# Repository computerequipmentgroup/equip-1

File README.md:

# Equip-1 ⚹ DV RECORDER

Equip-1 is an open-source, portable DV/HDV recorder for camcorders with FireWire/i.LINK/DV output. It is built around a Radxa ROCK 2F and a custom PCIe FireWire HAT, so you can mount it near a camera, power it from USB-C, press one button, and record tape footage directly to removable storage.

The project is for camera enthusiasts, videographers, film schools, archivists, and hardware/software contributors who want a modern, repairable path for capturing DV tapes without keeping an old laptop alive.

The [Firehat](https://github.com/computerequipmentgroup/firehat) is also available standalone. It works as a HAT for the ROCK 2F, Raspberry Pi 5, and other SBCs.

Website: <https://www.equip-1.c-e.group/>  
Community: [discord.gg/wpXmcb5mvK](https://discord.gg/wpXmcb5mvK)

## Features

- One-button DV/HDV capture from FireWire camcorders.
- On-device OLED/buttons UI + web based controls.
- Web UI controls for recording, video preview, file management and conversion settings.
- Full-quality `.mov`, `.dv`, `.avi`, or native HDV `.m2t` recordings.
- On-demand or automatic MP4 conversions for easy previewing and sharing.
- Optional MP4 deinterlacing for cleaner playback from interlaced DV sources.
- USB/SD capture storage handling, in-app updates, and HDMI preview support.

## Getting started

### 1. Download and flash a release image

The recommended way to get started is to use a prebuilt Equip-1 image from GitHub Releases.

1. Open the releases page: <https://github.com/computerequipmentgroup/equip-1/releases>
2. Download the latest image for your hardware; Equip-1 uses the Rock 2F image.
3. Install and open [balenaEtcher](https://etcher.balena.io/).
4. In Etcher, choose the Equip-1 image, choose your microSD card, then click **Flash**.
5. When flashing is complete, eject the card, insert it into Equip-1, and power the device over USB-C.

To build and flash an image from source instead:

```bash
./src/buildroot/scripts/build.sh
./src/buildroot/scripts/flash.sh
```

The default runtime settings are baked into the image from:

```text
src/buildroot/overlay/etc/equip1/equip-1.ini
```

On a running device, edit the live settings file at:

```text
/etc/equip1/equip-1.ini
```

### 2. Connect to Equip-1

Default device access:

| Setting        | Default                |
| -------------- | ---------------------- |
| Wi-Fi SSID     | `Equip-1`              |
| Wi-Fi password | `firesecret`           |
| Dashboard      | `http://10.42.0.1/`    |
| API base       | `http://10.42.0.1/api` |

Connect a phone or laptop to the Equip-1 Wi-Fi network, open the dashboard, attach a FireWire DV/HDV camera, and use the web UI or the device buttons to preview and record.

### 3. Prepare capture storage

Equip-1 records to `/data/captures` by default. At boot it prefers a non-root exFAT USB-A drive labelled `EQUIP1`; otherwise it falls back to the SD-card data partition. On a freshly flashed compressed image, first boot creates the missing SD-card recordings partition in the remaining free space, formats it as exFAT, labels it `EQUIP1`, and mounts it at `/data`.

Recommended capture storage format:

- filesystem: exFAT
- label: `EQUIP1`
- mount point on device: `/data`
- captures path: `/data/captures`

If automatic provisioning fails and the UI shows only rootfs-sized free space, create one exFAT partition labelled `EQUIP1` in the unallocated space after the flashed image partitions. Do not modify the boot/rootfs partitions and do not create two exFAT data partitions.

### 4. Record and export

Completed DV recordings are written as full-quality `.mov` captures by default, with settings for raw `.dv` or `.avi` containers. HDV sources still record as native `.m2t`. MP4 sidecars can be created on demand from settings, or automatically after each recording if auto-MP4 export is enabled.

MP4 quality presets:

| Setting    | OLED label | Use                                  |
| ---------- | ---------- | ------------------------------------ |
| `small`    | `[28]`     | Smallest files                       |
| `balanced` | `[23]`     | Middle ground                        |
| `high`     | `[18]`     | Close to source for most DV material |
| `max`      | `[14]`     | Highest quality, larger and slower   |

See [`src/docs/mp4-export.md`](src/docs/mp4-export.md) for the full export flow.

## Runtime settings

User-facing device settings live at `/etc/equip1/equip-1.ini`. The default file is staged from `src/buildroot/overlay/etc/equip1/equip-1.ini`, and matching `EQUIP1_*` environment variables can override INI values for development or one-off debugging.

Example:

```ini
[network]
ap_ssid = Equip-1
ap_password = firesecret

[recording]
capture_dir = /data/captures
storage_label = EQUIP1
recording_format = mov
auto_convert_mp4 = false
mp4_quality = high
mp4_deinterlace = true
auto_storage_switch = true

[hdmi]
enabled = true

[logging]
log_level = info
```

## Docs

The full source documentation lives in `src/docs/` and covers the runtime settings, capture pipeline, storage behavior, user interfaces, and Buildroot image. Start with the topic that matches what you are changing, then follow the linked references for lower-level implementation details.

- [`src/docs/runtime-settings.md`](src/docs/runtime-settings.md) — `/etc/equip1/equip-1.ini` sections, common keys, and environment overrides.
- [`src/docs/mp4-export.md`](src/docs/mp4-export.md) — MP4 sidecar export flow, OLED labels, and quality presets.
- [`src/docs/storage-captures-usb.md`](src/docs/storage-captures-usb.md) — capture storage, `/data/captures`, USB switching, and USB-C mass-storage mode.
- [`src/docs/buildroot-image.md`](src/docs/buildroot-image.md) — image build flow, rootfs overlay, init ordering, and runtime logs.
- [`src/docs/daemon-api.md`](src/docs/daemon-api.md) — daemon state model, commands, HTTP endpoints, streams, and WebSocket events.
- [`src/docs/dv-stream-recording-preview.md`](src/docs/dv-stream-recording-preview.md) — FireWire capture path, recording, browser preview, and HDMI/VLC output.
- [`src/docs/uis.md`](src/docs/uis.md) — OLED/buttons UI, browser dashboard, local designer, and static web build.
- [`src/docs/development-and-services.md`](src/docs/development-and-services.md) — local development workflows and Debian/Radxa service templates.
- [`src/docs/architecture.md`](src/docs/architecture.md) — how the daemon, shared stream, UIs, storage, and image overlay fit together.

## Hardware

- Radxa ROCK 2F (Rockchip RK3528A, quad-core ARM Cortex-A53, 2 GB RAM)
- [Firehat](https://github.com/computerequipmentgroup/firehat)
- MicroSD storage
- USB-C power input, 5 V
- HDMI output
- Wi-Fi 6, Bluetooth 5.4
- 2× USB 2.0 Type-A
- 60 mm × 70 mm × 25 mm, ~100 g

## Repository structure

This is an open-source hardware product repository. Editable product sources, generated manufacturing files, source code, and graphics assets are kept separate:

- `hw/` — electronics, mechanical design, manufacturing exports, and validation notes.
- `src/` — recorder daemon, OLED/web UIs, Buildroot image tooling, and development service templates.
- `gfx/` — renders, photos, product images, diagrams, screenshots, and logos.

Key source paths:

- `src/equip1d/` — FastAPI recorder daemon. Owns camera detection, `dvgrab`, deck control, capture storage, preview streaming, and recorder state.
- `src/uis/oled/` — 128×64 OLED/buttons frontend for on-device control.
- `src/uis/web/` — Nuxt static web dashboard for phone/laptop control over the local Equip-1 Wi-Fi AP.
- `src/buildroot/` — appliance image, kernel/boot fragments, rootfs overlay, init scripts, and flash/build tooling.
- `src/docs/` — architecture, runtime settings, Buildroot, storage, UI, and export notes.

## Development

Install Python dependencies:

```bash
python -m venv .venv
. .venv/bin/activate
pip install -r src/requirements.txt
```

Run the daemon locally:

```bash
PYTHONPATH=src python -m equip1d.main
```

Design OLED screens in a browser without hardware:

```bash
PYTHONPATH=src python -m uis.oled.designer
```

Open <http://127.0.0.1:8765>. The designer renders the real `src/uis/oled/screens.py` drawing code to a 128×64 PNG, with screen/scenario selectors, button simulation, and editable state JSON.

Build the web dashboard:

```bash
cd src/uis/web
npm install
npm run generate
```

The daemon serves `src/uis/web/.output/public` when it exists.

## Open source

Hardware is licensed under [CERN OHL-S](https://ohwr.org/cern_ohl_s_v2.txt). Software is licensed under GPL. Derivatives must be released under the same licenses.

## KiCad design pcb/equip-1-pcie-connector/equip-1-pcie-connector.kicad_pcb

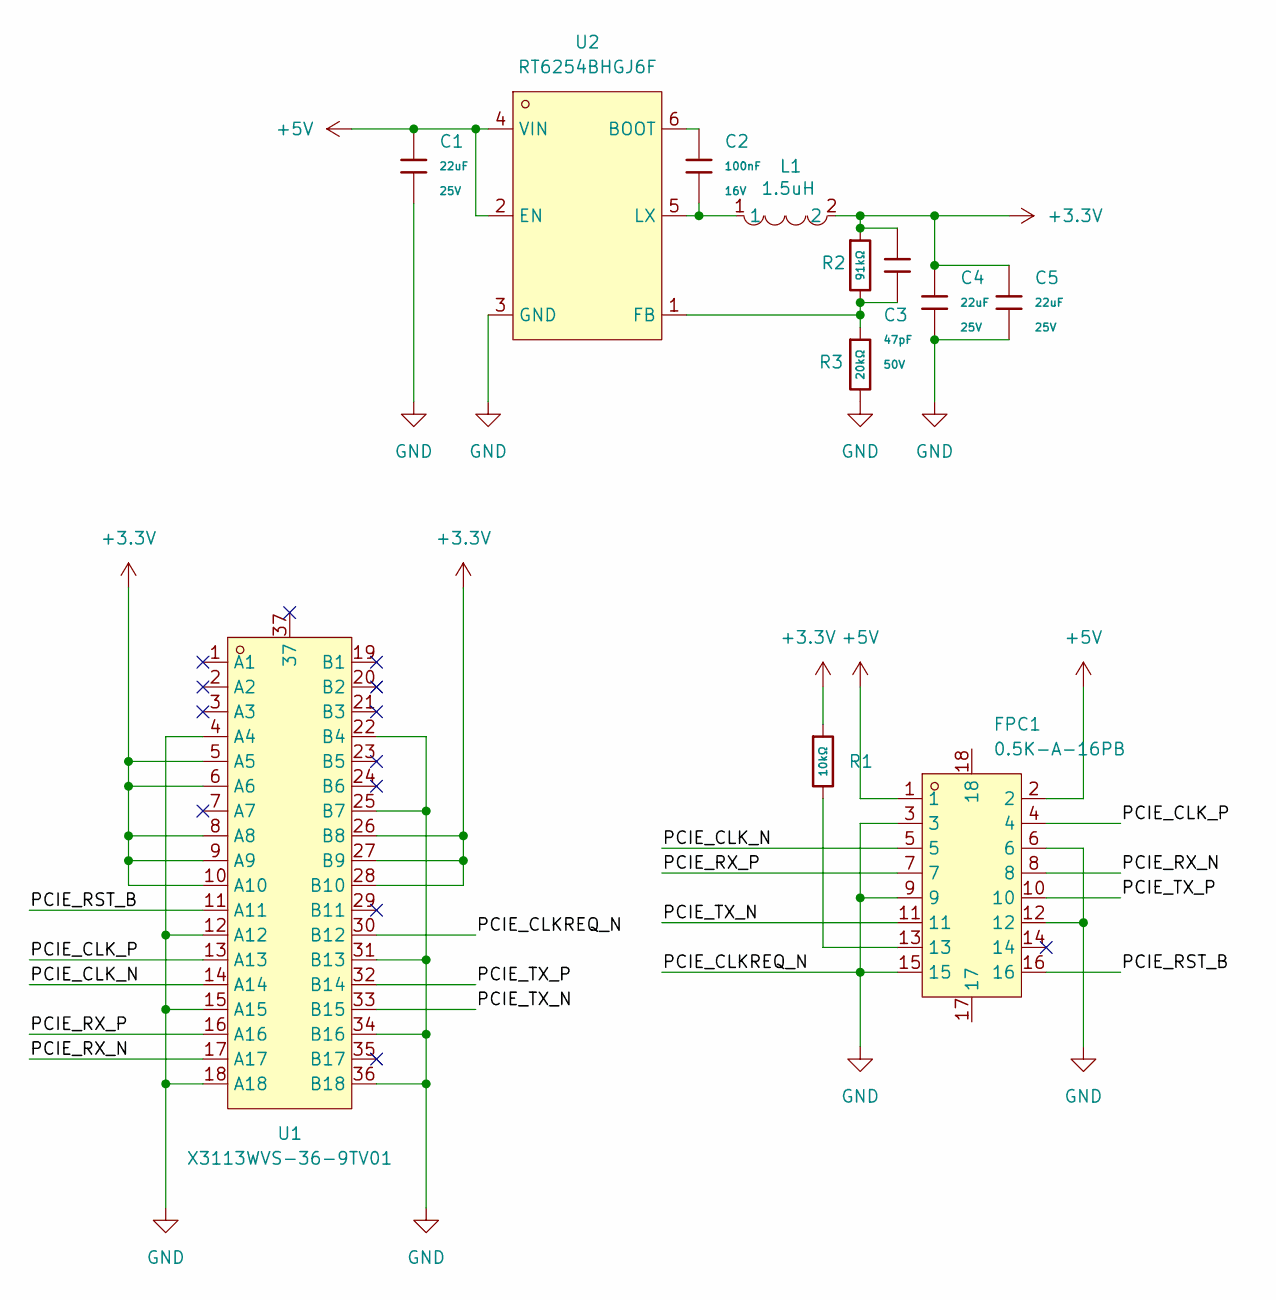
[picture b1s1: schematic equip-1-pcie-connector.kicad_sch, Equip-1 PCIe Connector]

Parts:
C1, C4, C5: 22uF; C_0805; Voltage Rated 25V; Tolerance ±20%; Part CL21A226MAQNNNE; LCSC C45783
C2: 100nF; C_0402; Voltage Rated 16V; Tolerance ±10%; Part CL05B104KO5NNNC; LCSC C1525
C3: 47pF; C_0402; Voltage Rated 50V; Tolerance ±5%; Part 0402CG470J500NT; LCSC C1567
FPC1: 0.5K-A-16PB; FPC-SMD_16P-P0.50_HDGC_0.5K-A-16PB; LCSC Part C2914142
L1: 1.5uH; IND-SMD_L4.4-W4.2; LCSC Part C167205
R1: 10kΩ; R_0603; Overload Voltage (Max) 75V; Tolerance ±1%; Part 0603WAF1002T5E; LCSC C25804
R2: 91kΩ; R_0603; Overload Voltage (Max) 75V; Tolerance ±1%; Part 0603WAF9102T5E; LCSC C23265
R3: 20kΩ; R_0603; Overload Voltage (Max) 75V; Tolerance ±1%; Part 0603WAF2002T5E; LCSC C4184
U1: X3113WVS-36-9TV01; CONN-SMD_X3113WVS-36-9TV01; LCSC Part C5711223
U2: RT6254BHGJ6F; TSOT-23-6_L2.9-W1.6-P0.95-LS2.8-BR; LCSC Part C3194280

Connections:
+3.3V: C3.1, C4.1, C5.1, L1.2, R1.1, R2.1, U1.5 (A5), U1.6 (A6), U1.8 (A8), U1.9 (A9), U1.10 (A10), U1.26 (B8), U1.27 (B9), U1.28 (B10)
+5V: C1.1, FPC1.1, FPC1.2, U2.2 (EN), U2.4 (VIN)
/PCIE_CLK_N: FPC1.5, U1.14 (A14)
/PCIE_CLK_P: FPC1.4, U1.13 (A13)
/PCIE_RST_B: FPC1.16, U1.11 (A11)
/PCIE_RX_N: FPC1.8, U1.17 (A17)
/PCIE_RX_P: FPC1.7, U1.16 (A16)
/PCIE_TX_N: FPC1.11, U1.33 (B15)
/PCIE_TX_P: FPC1.10, U1.32 (B14)
GND: C1.2, C4.2, C5.2, FPC1.3, FPC1.6, FPC1.9, FPC1.12, FPC1.15, R3.2, U1.4 (A4), U1.12 (A12), U1.15 (A15), U1.18 (A18), U1.22 (B4), U1.25 (B7), U1.30 (B12), U1.31 (B13), U1.34 (B16), U1.36 (B18), U2.3 (GND)
unnamed: FPC1.13, R1.2
unnamed: C2.1, U2.6 (BOOT)
unnamed: C3.2, R2.2, R3.1, U2.1 (FB)
unnamed: C2.2, L1.1, U2.5 (LX)

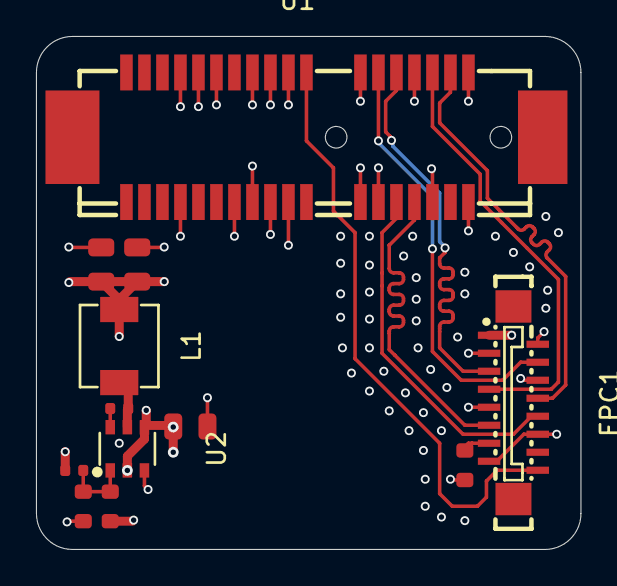
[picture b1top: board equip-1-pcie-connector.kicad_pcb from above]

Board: 4 copper layers, 30.2 x 28.5 mm, 12 parts (0 on the bottom side), 14 nets.

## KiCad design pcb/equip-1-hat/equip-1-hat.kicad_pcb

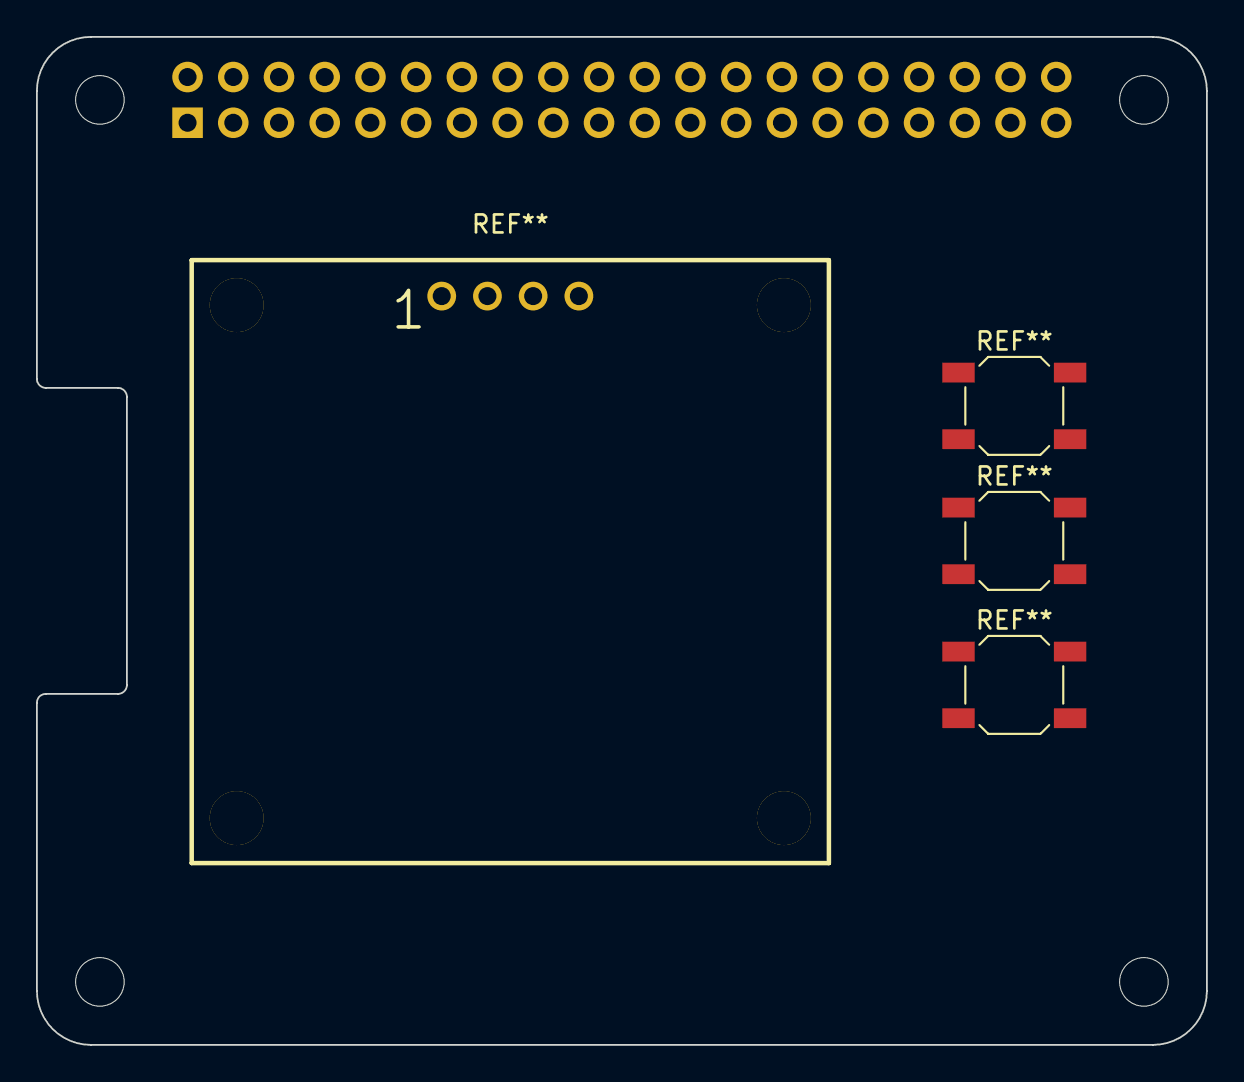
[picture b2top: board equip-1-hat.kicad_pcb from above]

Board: 2 copper layers, 65.0 x 56.0 mm, 5 parts (1 on the bottom side), 3 nets, no tracks yet.

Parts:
J1: GPIO; PinSocket_2x20_P2.54mm_Vertical
MH1, MH2, MH3, MH4: MountingHole_2.7mm_M2.5

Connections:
+3V3: J1.1, J1.17
+5V: J1.2, J1.4
GND: J1.6, J1.9, J1.14, J1.20, J1.25, J1.30, J1.34, J1.39

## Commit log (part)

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2025-04-10 added some notes
2025-04-10 format
2025-04-16 started pcb schematic
2025-04-24 updated documentation
2025-04-24 typo
2025-04-24 added image
2025-09-09 found parts, added to kicad
2025-09-09 schematic done
2025-09-09 routing done
2025-09-09 new layout..
2025-09-10 updated schematic for the buck
2025-09-10 added new ffc connector
2025-09-10 new buck controller
2025-09-10 new schematic done
2025-09-11 prototype done?
2025-09-11 ordered pcb ✅
2025-09-12 all togetha
2025-09-17 housekeeping
2025-09-17 we good
2025-09-17 added os dir
2025-09-17 added os ocde
2025-09-17 added button to os
2025-09-17 updated requirements.txt
2025-09-17 added right gpio pin
2025-09-20 readme
2025-09-20 discord push test
2025-09-20 we live and direct
2025-09-20 added armbian image download link
2025-09-21 inductor wrong value :(
2025-09-22 started working on firewire chip integration
2025-09-22 added portable setup to readme
2025-09-22 gif layout
2025-09-22 image width
